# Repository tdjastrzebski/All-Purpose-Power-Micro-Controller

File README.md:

# All-purpose Power Micro Controller

> Note: new, redesigned verion is in works: https://github.com/tdjastrzebski/All-Purpose-Micro-Controller-2
 
This general purpose power micro controller features:
* Wheatstone Bridge front-end
* New Texas Instruments [INA823](https://www.ti.com/product/INA823) instrumentation amplifier (see schematic for alternatives)
* Accurate Texas Instruments [REF2030](https://www.ti.com/product/REF2030) 1.5/3V dual reference voltage source (<0.05%, 1.5 ppm/°C typ.)
* 48-pin [STM32G0B1CE](https://www.st.com/en/microcontrollers-microprocessors/stm32g0b1ce.html) 512kB flash, 144 kB RAM MPU (64kB flash minimum - see schematic for alternatives)
* Popular [Waveshare 18179](https://www.waveshare.com/1.3inch-oled-module-c.htm) 128x64 1.3" OLED display
* [STLINK-V3](https://www.st.com/en/development-tools/stlink-v3mini.html) mini and STLINK-V2 debug connectors, Segger J-Link mini supported.
* Rotary encoder and EEPROM  
* Small dimensions - only 85x50mm

Optional components:
* USB socket, can be used as a power source
* Real Time Clock (RTC) with quartz crystal oscillator
* Miniature battery or supercapacitor for RTC and memory backup
* Opto-isolated serial port (RX/TX)
* I2C port
* Two buffered DACs
* Larger [Waveshare 14747](https://www.waveshare.com/1.5inch-rgb-oled-module.htm) 128x128 1.5" RGB OLED display
* Two potentiometers for fine-tuning (gain and zero)

The device has been designed to be easily configured - e.g. here as a **Weller WSP80** station/controller powered from a standard 30V/5A bench power supply. I have built this universal controller to test some design concepts and have used it intensively for over a year as a **Weller WSP80** soldering iron controller.  
Published schematic includes probably the final 3rd version, slightly improved over what is presented on the pictures (2nd version). Controller can be easily configured to work with any NPT/PPT thermistor or a thermo-couple.

Language: C/C++

Environment: Cube IDE, Cube MX or VS Code - see [VS Code Environment Setup](Software/EnvironmentSetup.md)

License:
* [Software](Software) is released under MIT license.
* [Hardware](Hardware) KiCad design is released under Attribution-NonCommercial-NoDerivatives 4.0 International (CC BY-NC-ND 4.0) License.

Reviews:
* [ANOTHER NEAT GENERAL PURPOSE SOLDERING IRON DRIVER](https://hackaday.com/2022/01/31/another-neat-general-purpose-soldering-iron-driver) by Dave Rowntree

Improvement ideas (help wanted):
* Detecting idle state by analyzing temperature fluctuations and implementing auto sleep mode.
* Implementing self-calibration (PWM duty cycle) algorithm to increase temp precision by analyzing rate of temperature growth.
* Eliminate PWM - it adds significant ripple to the measured signal.

This repo contains complete documentation. If you are interested in building this device and need more details, please let me know rising an issue on GitHub.  
Improvements, suggestions and PRs are more than welcome - rise GitHub issue.  
Finally, if you like this project do not hesitate to give it a star to let others know it is worth checking out.

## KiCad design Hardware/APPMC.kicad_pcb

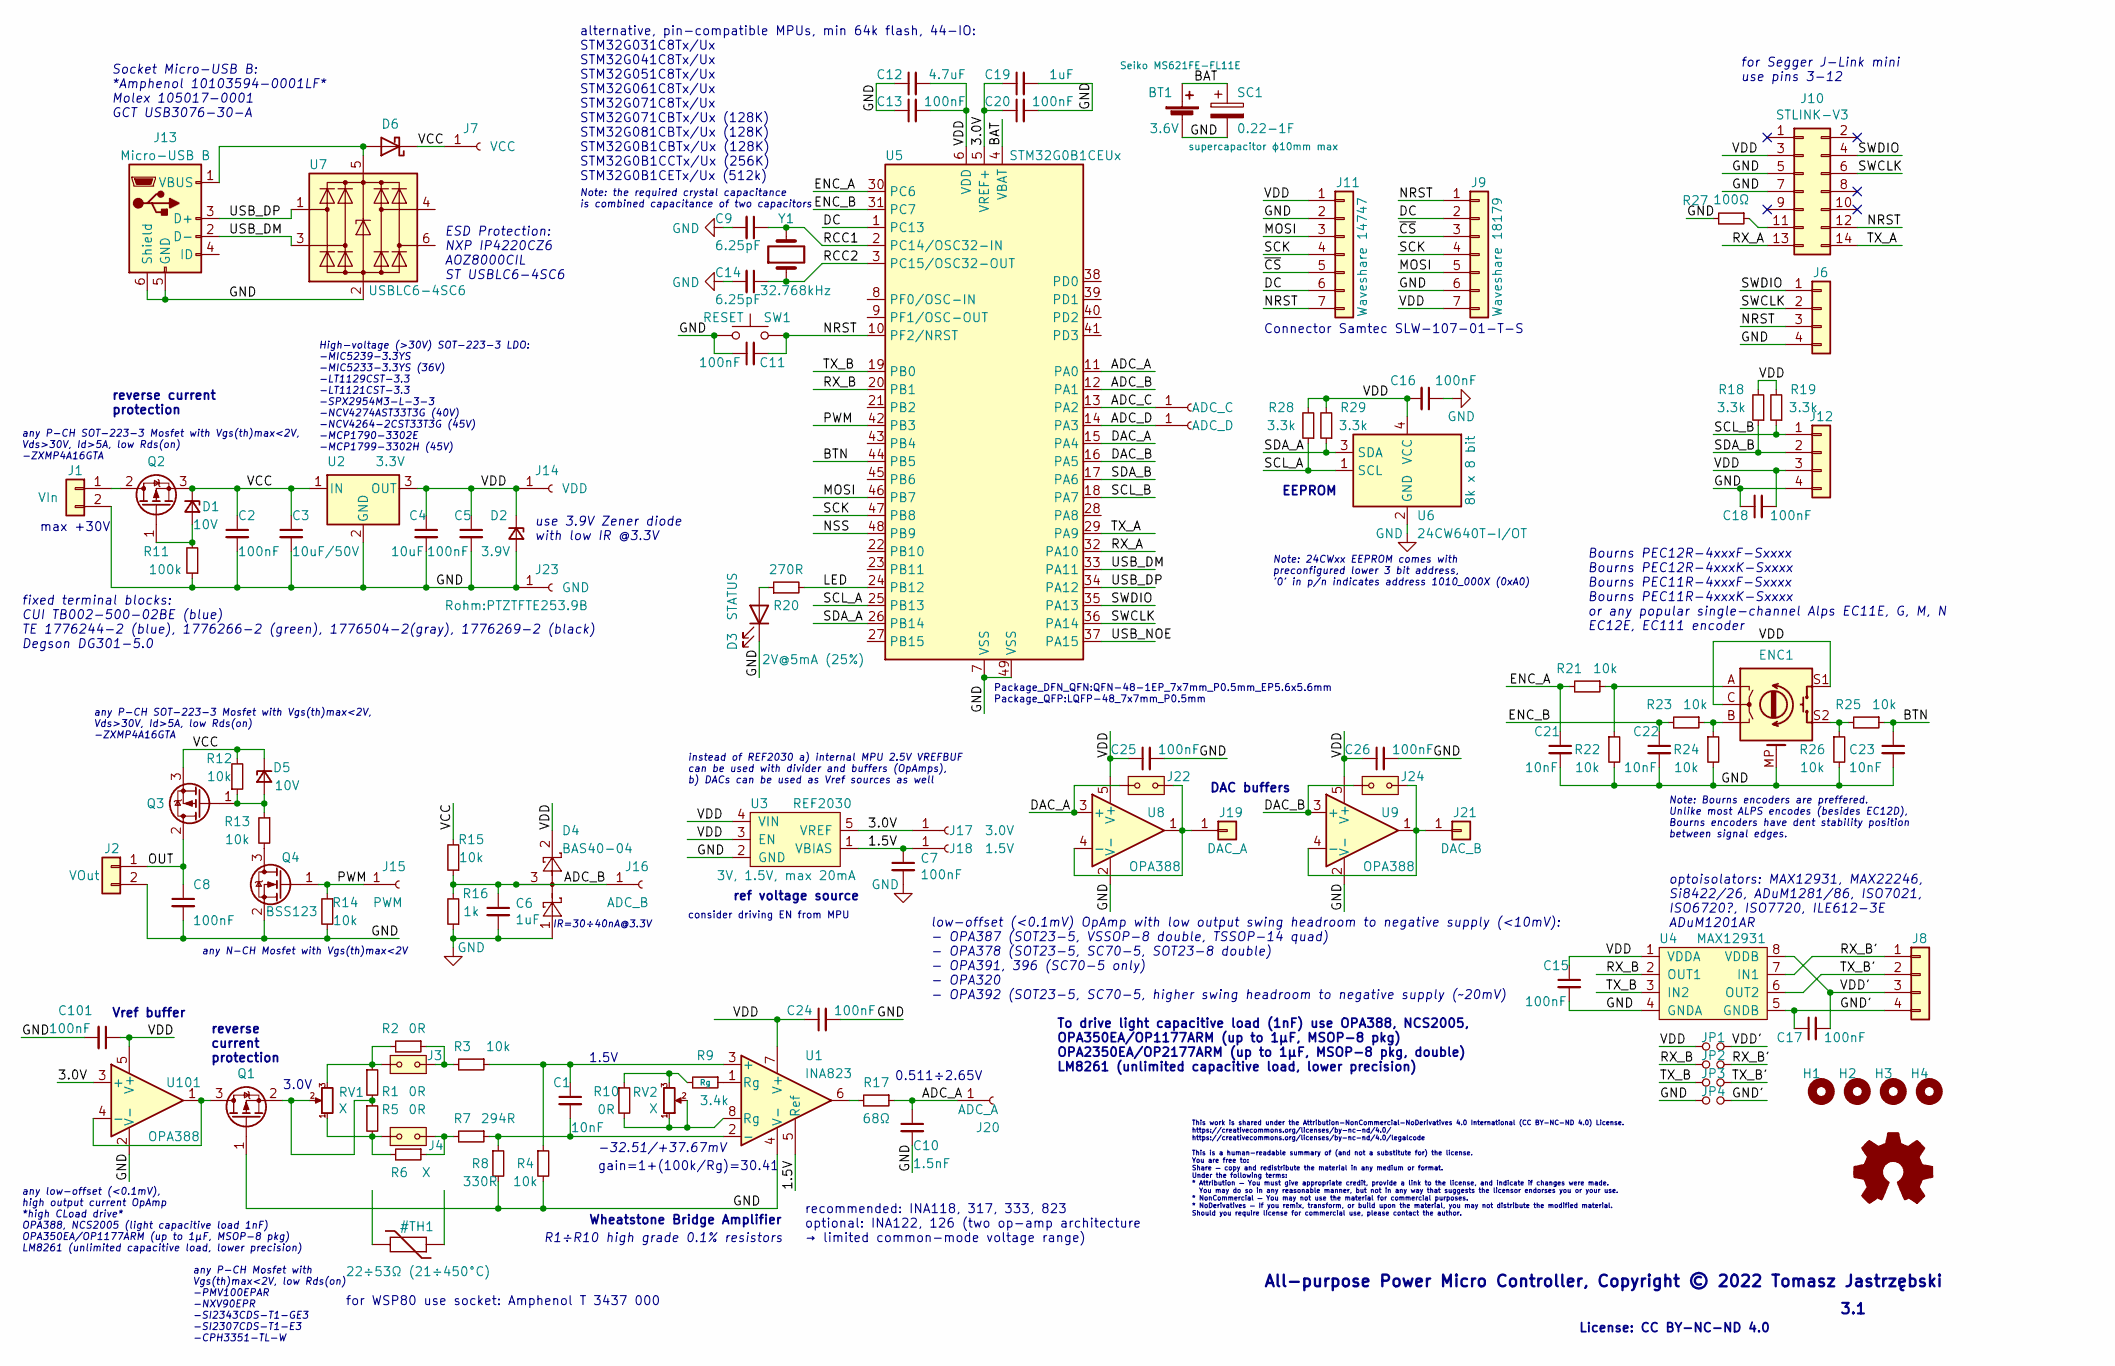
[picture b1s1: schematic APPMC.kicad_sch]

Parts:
BT1: Seiko MS621FE-FL11E; Seiko_MS621FE-FL11E
C1, C21, C22, C23: 10nF; C_0805_2012Metric_Pad1.15x1.40mm_HandSolder
C2, C8: 100nF; C_1210_3225Metric_Pad1.42x2.65mm_HandSolder
C3: 10uF/50V; C_1210_3225Metric_Pad1.42x2.65mm_HandSolder
C4: 10uF; C_0805_2012Metric_Pad1.15x1.40mm_HandSolder
C5, C7, C11, C13, C15, C16, C17, C18, C20, C24, C25, C26, C101: 100nF; C_0805_2012Metric_Pad1.15x1.40mm_HandSolder
C6, C19: 1uF; C_0805_2012Metric_Pad1.15x1.40mm_HandSolder
C9, C14: 6.25pF; C_0805_2012Metric_Pad1.15x1.40mm_HandSolder
C10: 1.5nF; C_0805_2012Metric_Pad1.15x1.40mm_HandSolder
C12: 4.7uF; C_0805_2012Metric_Pad1.15x1.40mm_HandSolder
D1: 10V; D_SOD-123F; Farnell 2069415
D2: 3.9V; D_SOD-123F; Farnell 2772457
D3: STATUS; D_0805_2012Metric_Pad1.15x1.40mm_HandSolder; Farnell 1318243
D4: BAS40-04; SOT-23; Farnell 2924692
D5: 10V; D_SOD-123F; Farnell 2069469
D6: D_Schottky; D_SOD-123F
ENC1: PEC16-4220F-S0024; RotaryEncoder_Alps_EC12E-Switch_Vertical_H20mm; Farnell 1520813
H1, H2, H3, H4: MountingHole; MountingHole_2.5mm_Pad_Via
J1: + 30V max; Degson_DG301-5.0-2
J2: VOut; Degson_DG301-5.0-2
J3, J4: Jumper-2B-Open; Degson_DG301-5.0-2
J6: STLINK-V2; PinHeader_1x04_P2.54mm_Vertical
J7: VCC; PinHeader_1x01_P2.54mm_Vertical
J8: Conn_01x04; PinHeader_1x04_P2.54mm_Vertical
J9: Waveshare 18179; WaveShare_18179
J10: STLINK-V3; PinHeader_2x07_P1.27mm_Vertical
J11: Waveshare 14747; WaveShare_14747_13992
J12: I2C; PinHeader_1x04_P2.54mm_Vertical
J13: Micro-USB B; USB_Micro-B_Amphenol_10103594-0001LF_Horizontal
J14: VDD; PinHeader_1x01_P1.27mm_Vertical
J15: PWM; PinHeader_1x01_P1.27mm_Vertical
J16: ADC_B; PinHeader_1x01_P1.27mm_Vertical
J17: 3.0V; PinHeader_1x01_P1.27mm_Vertical
J18: 1.5V; PinHeader_1x01_P1.27mm_Vertical
J19: DAC_A; PinHeader_1x01_P2.54mm_Vertical
J20: ADC_A; PinHeader_1x01_P1.27mm_Vertical
J21: DAC_B; PinHeader_1x01_P2.54mm_Vertical
J22, J24: Jumper-2B-Open; R_0805_2012Metric_Pad1.20x1.40mm_HandSolder_Jump
J23: GND; PinHeader_1x01_P2.54mm_Vertical
J101: ADC_C; PinHeader_1x01_P1.27mm_Vertical
J102: ADC_D; PinHeader_1x01_P1.27mm_Vertical
JP1, JP2, JP3, JP4: Jumper_NO_Small; Jumper_1x02_P1.27mm_Vertical
M4: Logo_Open_Hardware_Small; KiCad-Logo2_5mm_SilkScreen
Q1: SI2343CDS-T1-GE3; SOT-23; Farnell 2335290
Q2, Q3: ZXMP4A16GTA; SOT-223-3_TabPin2; Farnell 7564945
Q4: BSS123; TSOT-23; Farnell 9845321
R1, R5, R10: 0R; R_0805_2012Metric_Pad1.20x1.40mm_HandSolder_Jump
R2: 0R; R_0805_2012Metric_Jumper2.54
R3: 10k; R_0805_2012Metric_Pad1.20x1.40mm_HandSolder_Jump
R4: 10k; R_0805_2012Metric_Jumper2.54
R6: X; R_0805_2012Metric_Jumper2.54
R7: 294R; R_0805_2012Metric_Pad1.20x1.40mm_HandSolder_Jump
R8: 330R; R_0805_2012Metric_Jumper2.54
R9: 3.4k; R_0805_2012Metric_Pad1.20x1.40mm_HandSolder_Jump
R11: 100k; R_0805_2012Metric_Pad1.15x1.40mm_HandSolder
R12, R13, R14, R15, R21, R22, R23, R24, R25, R26: 10k; R_0805_2012Metric_Pad1.15x1.40mm_HandSolder
R16: 1k; R_0805_2012Metric_Pad1.15x1.40mm_HandSolder
R17: 68Ω; R_0805_2012Metric_Pad1.15x1.40mm_HandSolder
R18, R19, R28, R29: 3.3k; R_0805_2012Metric_Pad1.15x1.40mm_HandSolder
R20: 270R; R_0805_2012Metric_Pad1.15x1.40mm_HandSolder
R27: 100Ω; R_0805_2012Metric_Pad1.15x1.40mm_HandSolder
RV1, RV2: X; Bourns_3296WXYZ
SC1: 0.22-1F; CP_Radial_D10.0mm_P5.00mm
SW1: RESET; C&K_PTS636
U1: INA823; SOIC-8_3.9x4.9mm_P1.27mm
U2: 3.3V; SOT-223-3_TabPin2; Farnell 2857635
U3: REF2030; SOT-23-5; Farnell 3124516
U4: MAX12931; SOIC-8_3.9x4.9mm_P1.27mm
U5: STM32G0B1CEUx; QFN-48-1EP_7x7mm_P0.5mm_EP5.6x5.6mm
U6: 24CW640T-I/OT; SOT-23-5
U7: USBLC6-4SC6; SOT-23-6
U8, U9, U101: OPA388; SOT-23-5
Y1: 32.768kHz; Abracon_ABS07-HS

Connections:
/1.5V: C7.1, J18.1, U1.5 (Ref), U3.1 (VBIAS)
/3.0V: C19.1, C20.1, J17.1, U3.5 (VREF), U5.5 (VREF+), U101.3 (+)
/ADC_A: C10.1, J20.1, R17.1, U5.11 (PA0)
/ADC_B: C6.1, D4.3, J16.1, R15.1, R16.2, U5.12 (PA1)
/ADC_C: J101.1, U5.13 (PA2)
/ADC_D: J102.1, U5.14 (PA3)
/BAT: BT1.1 (+), SC1.1, U5.4 (VBAT)
/BTN: C23.1, R25.1, U5.44 (PB5)
/DAC_A: J22.1, U5.15 (PA4), U8.3 (+)
/DAC_B: J24.1, U5.16 (PA5), U9.3 (+)
/DC: J9.2, J11.6, U5.1 (PC13)
/ENC_A: C21.1, R21.2, U5.30 (PC6)
/ENC_B: C22.1, R23.2, U5.31 (PC7)
/GND': C17.1, J8.4, JP4.2, U4.5 (GNDB)
/LED: R20.2, U5.24 (PB12)
/MOSI: J9.5, J11.3, U5.46 (PB7)
/NRST: C11.2, J6.3, J9.1, J10.12, J11.7, SW1.1, U5.10 (PF2/NRST)
/OUT: C8.1, J2.1, Q3.2 (D)
/PWM: J15.1, Q4.1 (G), R14.1, U5.42 (PB3)
/RCC1: C9.1, U5.2 (PC14/OSC32-IN), Y1.2
/RCC2: C14.1, U5.3 (PC15/OSC32-OUT), Y1.1
/RX_A: J10.13, U5.32 (PA10)
/RX_B: JP2.1, U4.2 (OUT1), U5.20 (PB1)
/RX_B': J8.1, JP2.2, U4.7 (IN1)
/SCK: J9.4, J11.4, U5.47 (PB8)
/SCL_A: R28.1, U5.25 (PB13), U6.1 (SCL)
/SCL_B: J12.1, R19.1, U5.18 (PA7)
/SDA_A: R29.1, U5.26 (PB14), U6.3 (SDA)
/SDA_B: J12.2, R18.1, U5.17 (PA6)
/SWCLK: J6.2, J10.6, U5.36 (PA14)
/SWDIO: J6.1, J10.4, U5.35 (PA13)
/TX_A: J10.14, U5.29 (PA9)
/TX_B: JP3.1, U4.3 (IN2), U5.19 (PB0)
/TX_B': J8.2, JP3.2, U4.6 (OUT2)
/USB_DM: J13.2 (D-), U5.33 (PA11), U7.3 (I/O2)
/USB_DP: J13.3 (D+), U5.34 (PA12), U7.1 (I/O1)
/VCC: C2.1, C3.1, D1.1 (K), D5.1 (K), D6.1 (K), J7.1, Q2.3 (S), Q3.3 (S), R12.2, R15.2, U2.1 (IN)
/VDD: C4.1, C5.1, C12.2, C13.2, C15.1, C16.2, C18.2, C24.1, C25.1, C26.1, C101.1, D2.1 (K), D4.2, ENC1.C, ENC1.S1, J9.7, J10.3, J11.1, J12.3, J14.1, JP1.1, R18.2, R19.2, R28.2, R29.2, U1.7 (V+), U2.3 (OUT), U3.3 (EN), U3.4 (VIN), U4.1 (VDDA), U5.6 (VDD), U6.4 (VCC), U8.5 (V+), U9.5 (V+), U101.5 (V+)
/VDD': C17.2, J8.3, JP1.2, U4.8 (VDDB)
/~CS: J9.3, J11.5
GND: BT1.2 (-), C2.2, C3.2, C4.2, C5.2, C6.2, C7.2, C8.2, C9.2, C10.2, C11.1, C12.1, C13.1, C14.2, C15.2, C16.1, C18.1, C19.2, C20.2, C21.2, C22.2, C23.2, C24.2, C25.2, C26.2, C101.2, D2.2 (A), D3.1 (K), D4.1, ENC1.MP, J1.2, J2.2, J6.4, J9.6, J10.5, J10.7, J11.2, J12.4, J13.5 (GND), J13.6 (Shield), J23.1, JP4.1, Q1.1 (G), Q4.2 (S), R4.2, R8.2, R11.1, R14.2, R16.1, R22.2, R24.2, R26.2, R27.2, SC1.2, SW1.2, U1.4 (V-), U2.2 (GND), U3.2 (GND), U4.4 (GNDA), U5.7 (VSS), U5.49 (VSS), U6.2 (GND), U7.2 (GND), U8.2 (V-), U9.2 (V-), U101.2 (V-)
unnamed: C1.1, R3.1, R4.1, U1.3 (+)
unnamed: C1.2, R7.1, R8.1, U1.2 (-)
unnamed: D1.2 (A), Q2.1 (G), R11.2
unnamed: D3.2 (A), R20.1
unnamed: D5.2 (A), Q3.1 (G), R12.1, R13.1
unnamed: D6.2 (A), J13.1 (VBUS), U7.5 (VBUS)
unnamed: ENC1.A, R21.1, R22.1
unnamed: ENC1.B, R23.1, R24.1
unnamed: ENC1.S2, R25.2, R26.1
unnamed: J1.1, Q2.2 (D)
unnamed: J3.1, R2.1, R3.2
unnamed: J3.2, R1.1, R2.2, RV1.3
unnamed: J4.1, R5.2, R6.2, RV1.1
unnamed: J4.2, R6.1, R7.2
unnamed: J10.11, R27.1
unnamed: J19.1, J22.2, U8.1, U8.4 (-)
unnamed: J21.1, J24.2, U9.1, U9.4 (-)
unnamed: Q1.2 (S), R1.2, R5.1, RV1.2
unnamed: Q1.3 (D), U101.1, U101.4 (-)
unnamed: Q4.3 (D), R13.2
unnamed: R9.1, U1.1 (Rg)
unnamed: R9.2, R10.1, RV2.3
unnamed: R10.2, RV2.1, RV2.2, U1.8 (Rg)
unnamed: R17.2, U1.6

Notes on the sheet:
DAC buffers
ESD Protection: NXP IP4220CZ6 AOZ8000CIL ST USBLC6-4SC6
use 3.9V Zener diode with low IR @3.3V
Connector Samtec SLW-107-01-T-S
All-purpose Power Micro Controller, Copyright © 2022 Tomasz Jastrzębski
ref voltage source
for Segger J-Link mini use pins 3-12
fixed terminal blocks: CUI TB002-500-02BE (blue) TE 1776244-2 (blue), 1776266-2 (green), 1776504-2(gray), 1776269-2 (black) Degson DG301-5.0
reverse current protection
1.5V
Wheatstone Bridge Amplifier
any P-CH SOT-223-3 Mosfet with Vgs(th)max<2V, Vds>30V, Id>5A, low Rds(on) -ZXMP4A16GTA
recommended: INA118, 317, 333, 823 optional: INA122, 126 (two op-amp architecture → limited common-mode voltage range)
low-offset (<0.1mV) OpAmp with low output swing headroom to negative supply (<10mV): - OPA387 (SOT23-5, VSSOP-8 double, TSSOP-14 quad) - OPA378 (SOT23-5, SC70-5, SOT23-8 double) - OPA391, 396 (SC70-5 only) - OPA320 - OPA392 (SOT23-5, SC70-5, higher swing headroom to negative supply (~20mV)
3.0V
Bourns PEC12R-4xxxF-Sxxxx Bourns PEC12R-4xxxK-Sxxxx Bourns PEC11R-4xxxF-Sxxxx Bourns PEC11R-4xxxK-Sxxxx or any popular single-channel Alps EC11E, G, M, N EC12E, EC111 encoder
any low-offset (<0.1mV), high output current OpAmp *high CLoad drive* OPA388, NCS2005 (light capacitive load 1nF) OPA350EA/OP1177ARM (up to 1µF, MSOP-8 pkg) LM8261 (unlimited capacitive load, lower precision)
3.1
License: CC BY-NC-ND 4.0
EEPROM
instead of REF2030 a) internal MPU 2.5V VREFBUF can be used with divider and buffers (OpAmps), b) DACs can be used as Vref sources as well
This work is shared under the Attribution-NonCommercial-NoDerivatives 4.0 International (CC BY-NC-ND 4.0) License. https://creativecommons.org/licenses/by-nc-nd/4.0/ https://creativecommons.org/licenses/by-nc-nd/4.0/legalcode This is a human-readable summary of (and not a substitute for) the licens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
max +30V
-32.51/+37.67mV
R1÷R10 high grade 0.1% resistors
alternative, pin-compatible MPUs, min 64k flash, 44-IO: STM32G031C8Tx/Ux STM32G041C8Tx/Ux STM32G051C8Tx/Ux STM32G061C8Tx/Ux STM32G071C8Tx/Ux STM32G071CBTx/Ux (128K) STM32G081CBTx/Ux (128K) STM32G0B1CBTx/Ux (128K) STM32G0B1CCTx/Ux (256K) STM32G0B1CETx/Ux (512k)
Socket Micro-USB B: *Amphenol 10103594-0001LF* Molex 105017-0001 GCT USB3076-30-A
Note: 24CWxx EEPROM comes with preconfigured lower 3 bit address, '0' in p/n indicates address 1010_000X (0xA0)
optoisolators: MAX12931, MAX22246, Si8422/26, ADuM1281/86, ISO7021, ISO6720?, ISO7720, ILE612-3E ADuM1201AR
IR=30÷40nA@3.3V
reverse current protection
High-voltage (>30V) SOT-223-3 LDO: -MIC5239-3.3YS -MIC5233-3.3YS (36V) -LT1129CST-3.3 -LT1121CST-3.3 -SPX2954M3-L-3-3 -NCV4274AST33T3G (40V) -NCV4264-2CST33T3G (45V) -MCP1790-3302E -MCP1799-3302H (45V)
0.511÷2.65V
Note: Bourns encoders are preffered. Unlike most ALPS encodes (besides EC12D), Bourns encoders have dent stability position between signal edges.
consider driving EN from MPU
Vref buffer
any P-CH Mosfet with Vgs(th)max<2V, low Rds(on) -PMV100EPAR -NXV90EPR -SI2343CDS-T1-GE3 -SI2307CDS-T1-E3 -CPH3351-TL-W
To drive light capacitive load (1nF) use OPA388, NCS2005, OPA350EA/OP1177ARM (up to 1µF, MSOP-8 pkg) OPA2350EA/OP2177ARM (up to 1µF, MSOP-8 pkg, double) LM8261 (unlimited capacitive load, lower precision)
Note: the required crystal capacitance is combined capacitance of two capacitors
any N-CH Mosfet with Vgs(th)max<2V

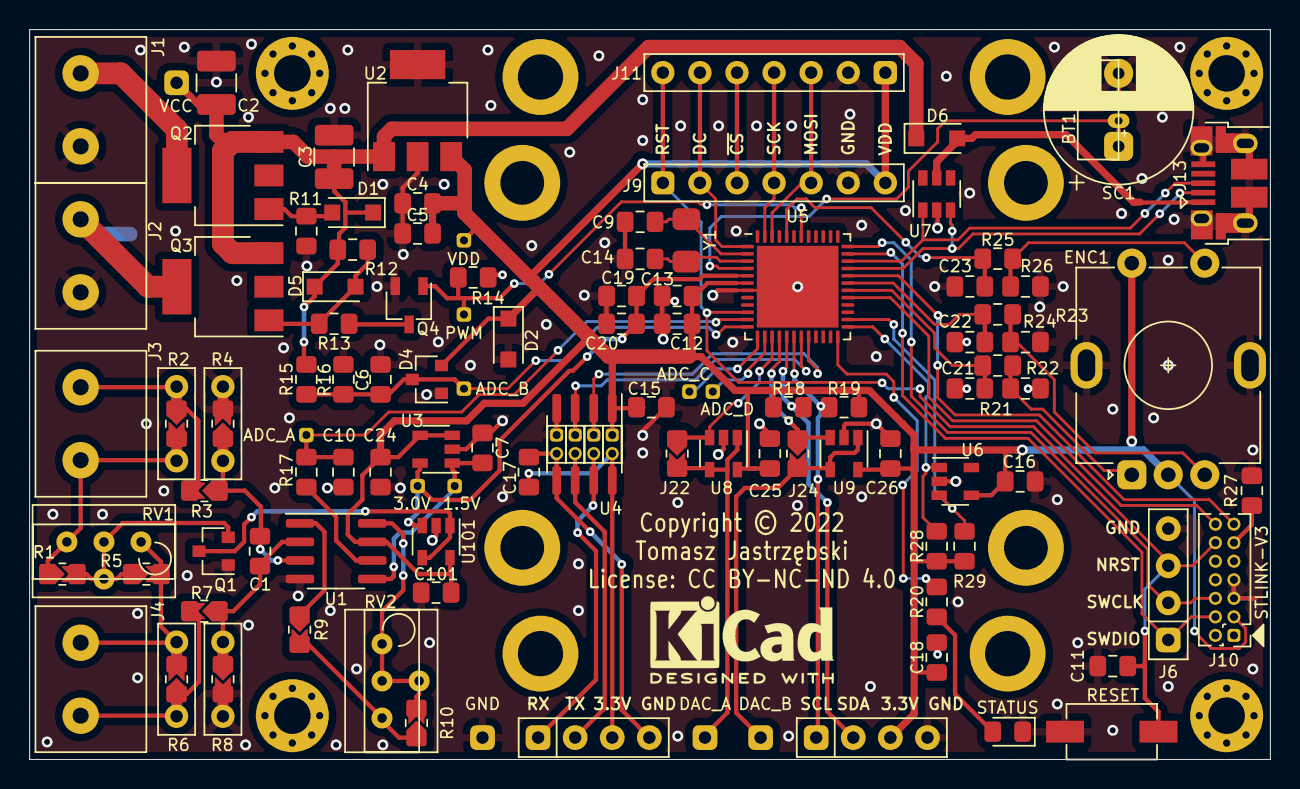
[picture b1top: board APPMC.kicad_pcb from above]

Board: 2 copper layers, 85.0 x 50.0 mm, 117 parts (1 on the bottom side), 65 nets.

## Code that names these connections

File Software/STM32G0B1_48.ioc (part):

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Mcu.Name=STM32G0B1C(B-C-E)Ux
Mcu.Package=UFQFPN48
Mcu.UserName=STM32G0B1CEUx
PA0.GPIOParameters=GPIO_Label
PA0.GPIO_Label=ADC_A
PA0.Mode=IN0
PA0.Signal=ADC1_IN0
PA1.GPIOParameters=GPIO_Label
PA1.GPIO_Label=ADC_B
PA1.Mode=IN1
PA1.Signal=ADC1_IN1
PA10.GPIOParameters=GPIO_Label
PA10.GPIO_Label=RX_A
PA10.Mode=Asynchronous
PA10.Signal=USART1_RX
PA11\ [PA9].Mode=Device
PA11\ [PA9].Signal=USB_DM
PA12\ [PA10].Mode=Device
PA12\ [PA10].Signal=USB_DP
PA13.GPIOParameters=GPIO_Label
PA13.GPIO_Label=SWDIO
PA13.Mode=Serial_Wire
PA13.Signal=SYS_SWDIO
PA14-BOOT0.GPIOParameters=GPIO_Label
PA14-BOOT0.GPIO_Label=SWCLK
PA14-BOOT0.Mode=Serial_Wire
PA14-BOOT0.Signal=SYS_SWCLK
PA4.GPIOParameters=GPIO_Label
PA4.GPIO_Label=DAC_A
PA4.Signal=COMP_DAC11_group
PA5.GPIOParameters=GPIO_Label
PA5.GPIO_Label=DAC_B
PA5.Signal=COMP_DAC12_group
PA6.GPIOParameters=GPIO_Label
PA6.GPIO_Label=SDA_B
PA6.Mode=I2C
PA6.Signal=I2C3_SDA
PA7.GPIOParameters=GPIO_Label
PA7.GPIO_Label=SCL_B
PA7.Mode=I2C
PA7.Signal=I2C3_SCL
PA9.GPIOParameters=GPIO_Label
PA9.GPIO_Label=TX_A
PA9.Mode=Asynchronous
PA9.Signal=USART1_TX
PB0.GPIOParameters=GPIO_Label
PB0.GPIO_Label=TX_B
PB0.Mode=Asynchronous
PB0.Signal=USART5_TX
PB1.GPIOParameters=GPIO_Label
PB1.GPIO_Label=RX_B
PB1.Mode=Asynchronous
PB1.Signal=USART5_RX
PB12.GPIOParameters=GPIO_PuPd,GPIO_Label,GPIO_ModeDefaultOutputPP
PB12.GPIO_Label=LED
PB12.GPIO_ModeDefaultOutputPP=GPIO_MODE_OUTPUT_PP
PB12.GPIO_PuPd=GPIO_NOPULL
PB12.Signal=GPIO_Output
PB13.GPIOParameters=GPIO_Label
PB13.GPIO_Label=SCL_A
PB13.Mode=I2C
PB13.Signal=I2C2_SCL
PB14.GPIOParameters=GPIO_Label
PB14.GPIO_Label=SDA_A
PB14.Mode=I2C
PB14.Signal=I2C2_SDA
PB3.GPIOParameters=GPIO_Label
PB3.GPIO_Label=PWM
PB3.Signal=S_TIM1_CH2
PB5.GPIOParameters=GPIO_Label
PB5.GPIO_Label=BTN
PB5.Signal=GPXTI5
PB7.GPIOParameters=GPIO_Label
PB7.GPIO_Label=MOSI
PB7.Mode=TX_Only_Simplex_Unidirect_Master
PB7.Signal=SPI2_MOSI
PB8.GPIOParameters=GPIO_Label
PB8.GPIO_Label=SCK
PB8.Mode=TX_Only_Simplex_Unidirect_Master
PB8.Signal=SPI2_SCK
PB9.GPIOParameters=GPIO_Label
PB9.GPIO_Label=CS
PB9.Mode=NSS_Signal_Hard_Output
PB9.Signal=SPI2_NSS
PC13.GPIOParameters=GPIO_Label
PC13.GPIO_Label=DC
PC13.Signal=GPIO_Output
PC6.GPIOParameters=GPIO_Label
PC6.GPIO_Label=ENC2
PC6.Signal=S_TIM3_CH1
PC7.GPIOParameters=GPIO_Label
PC7.GPIO_Label=ENC1
PC7.Signal=S_TIM3_CH2
RCC.HSE_VALUE=8000000
RCC.SYSCLKFreq_VALUE=16000000
board=custom

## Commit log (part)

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2022-01-29 initial version
2022-01-29 size adjusted
2022-01-29 wording fix
2022-01-30 docs/license info update
2022-01-31 wording
2022-02-03 fixes, improvements
2022-02-03 references update
2022-02-03 docs update
2022-02-05 fixes, updates
2022-02-05 readme update
2022-02-05 docs fix
2022-02-05 MPU list errata
2022-02-05 values adjusted
2022-02-06 images update
2022-02-06 docs & VS Code settings update
2022-02-06 settings cleanup
2022-02-08 updates to 3.1
2022-02-09 Update master.cpp
    Add proper c-linkage to public functions that need to be linked with c-code
2022-09-14 2022-09
2022-09-17 readme, tasks and launch update
2022-09-18 launch and tasks update
2022-09-18 launch update
2023-07-07 build file and VS Code settings fix
